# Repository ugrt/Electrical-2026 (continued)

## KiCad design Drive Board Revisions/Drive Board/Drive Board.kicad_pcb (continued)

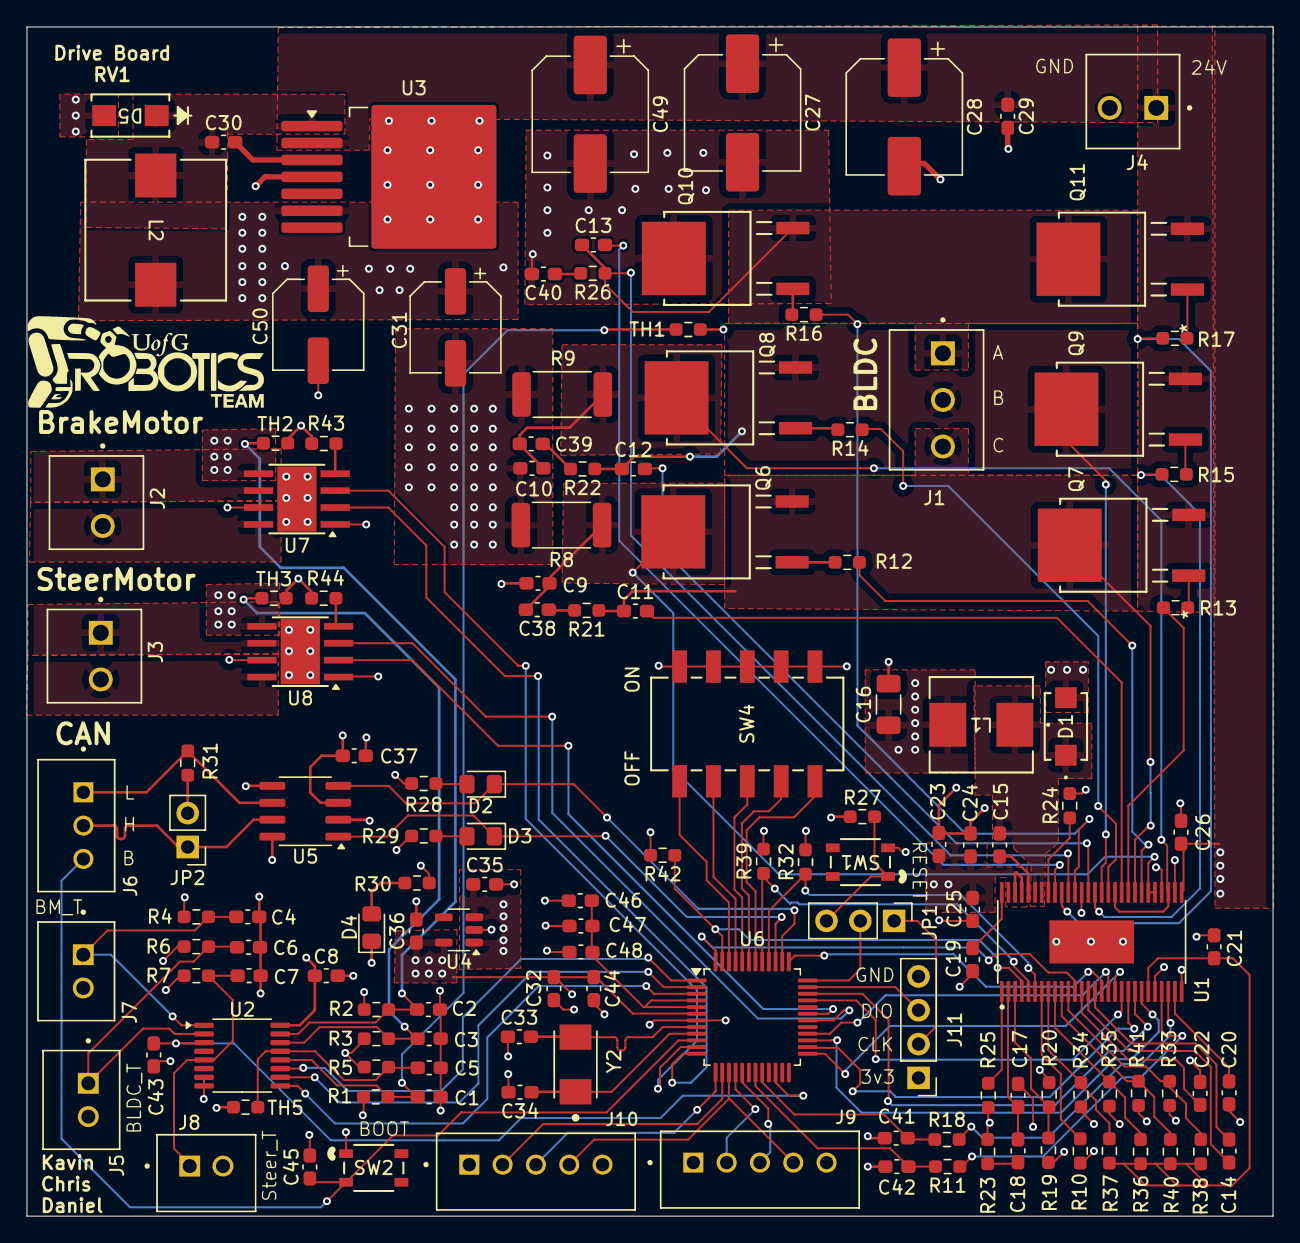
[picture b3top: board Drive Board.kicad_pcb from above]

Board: 4 copper layers, 93.5 x 89.3 mm, 136 parts (0 on the bottom side), 109 nets.

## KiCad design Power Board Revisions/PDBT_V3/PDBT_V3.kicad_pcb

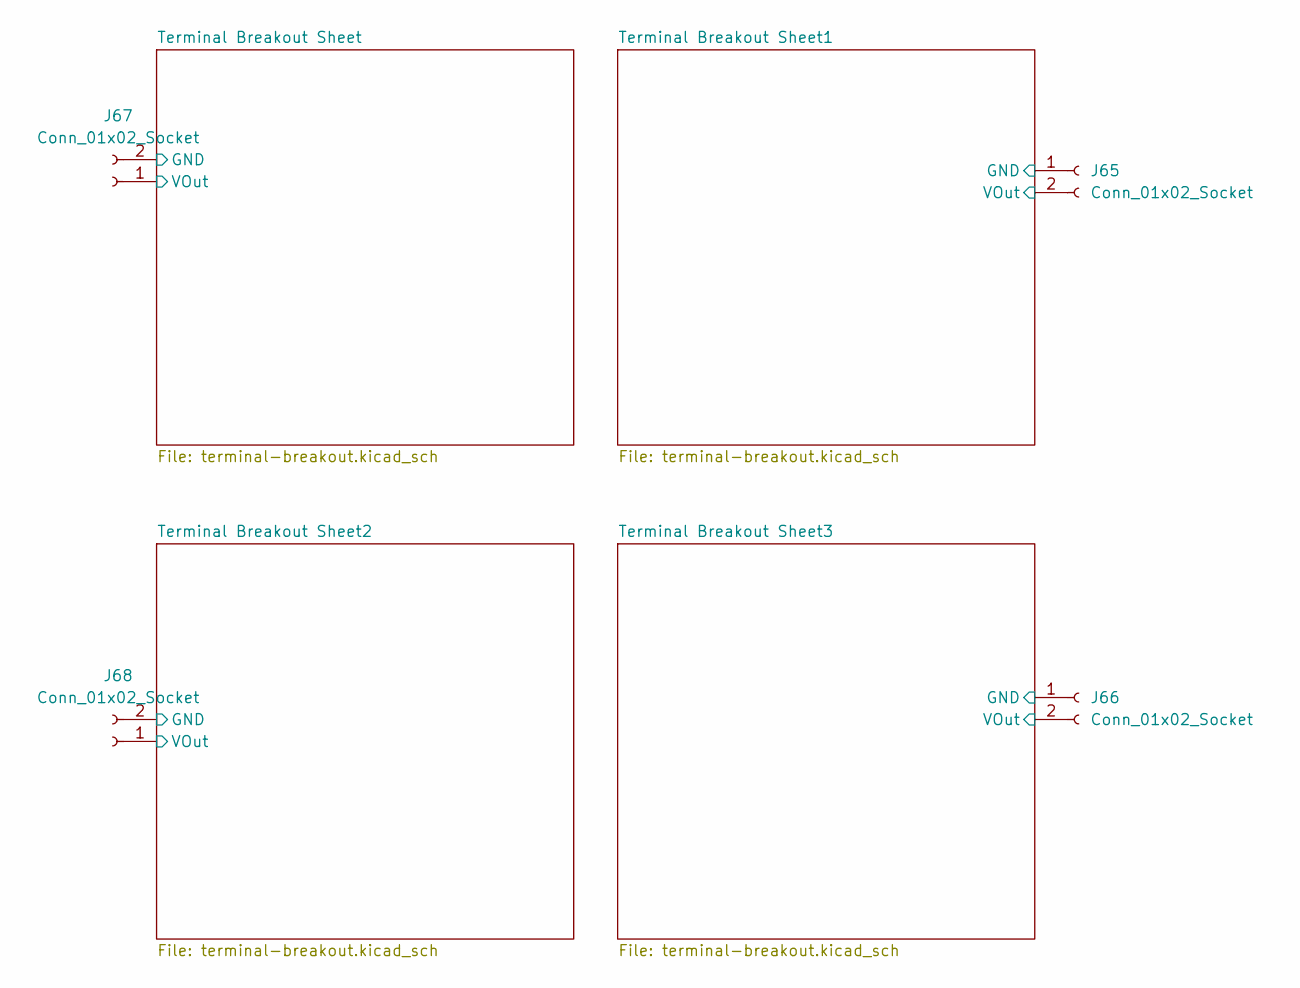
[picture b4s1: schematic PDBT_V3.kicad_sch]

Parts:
J65, J66, J67, J68: Conn_01x02_Socket; AMASS_XT60-F_1x02_P7.20mm_Vertical

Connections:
/Terminal Breakout Sheet1/VOut: J65.2; also elsewhere on the board
/Terminal Breakout Sheet2/VOut: J68.1; also elsewhere on the board
/Terminal Breakout Sheet3/VOut: J66.2; also elsewhere on the board
/Terminal Breakout Sheet/VOut: J67.1; also elsewhere on the board
GND: J65.1, J66.1, J67.2, J68.2; also elsewhere on the board

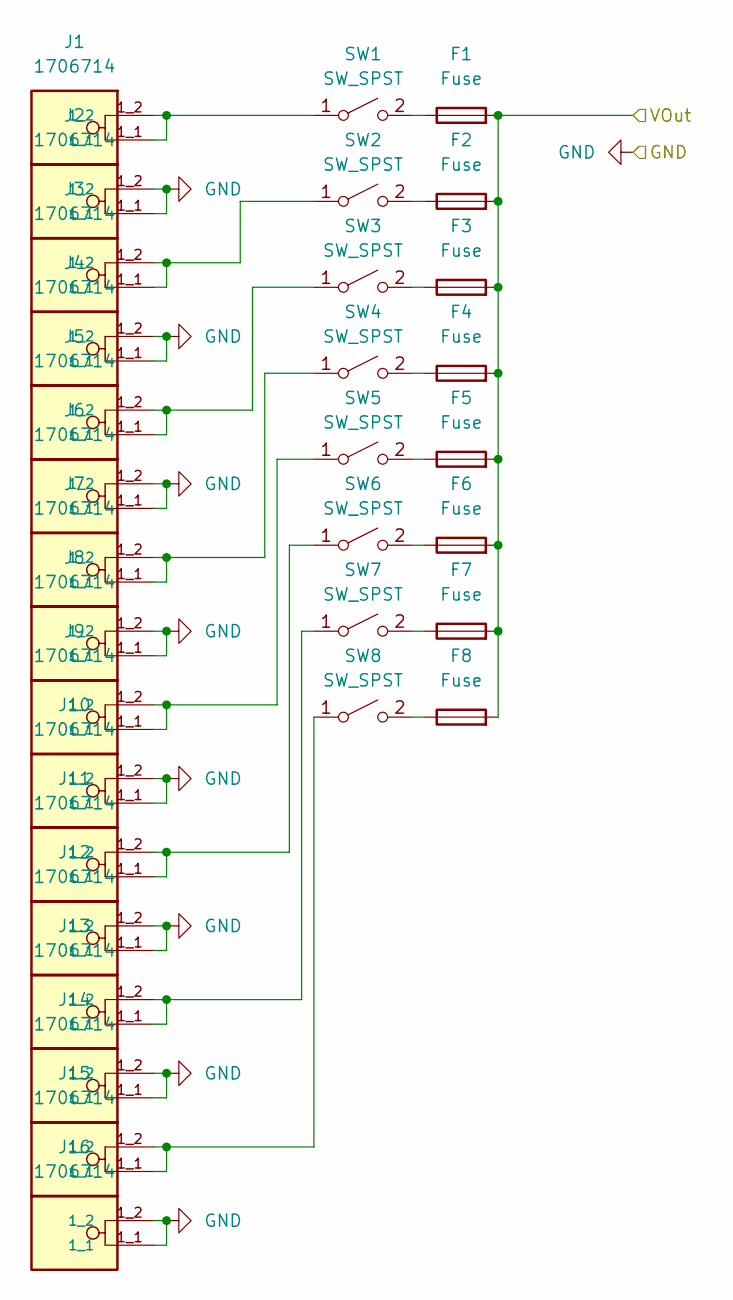
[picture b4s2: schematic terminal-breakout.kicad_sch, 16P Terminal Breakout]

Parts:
F1, F2, F3, F4, F5, F6, F7, F8: Fuse; FUSE_3557-2; DigiKey_Part_Number 36-3557-2-ND
J1, J2, J3, J4, J5, J6, J7, J8, J9, J10, J11, J12, J13, J14, J15, J16: 1706714; Phoenix 1706714; PARTREV 08.12.2022
SW1, SW2, SW3, SW4, SW5, SW6, SW7, SW8: SW_SPST; ESwitch 1101A4CQEA

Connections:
/Terminal Breakout Sheet/VOut: F1.2, F2.2, F3.2, F4.2, F5.2, F6.2, F7.2, F8.2; also elsewhere on the board
GND: J2.1_1, J2.1_2, J4.1_1, J4.1_2, J6.1_1, J6.1_2, J8.1_1, J8.1_2, J10.1_1, J10.1_2, J12.1_1, J12.1_2, J14.1_1, J14.1_2, J16.1_1, J16.1_2; also elsewhere on the board
unnamed: J1.1_1, J1.1_2, SW1.1 (A)
unnamed: F1.1, SW1.2 (B)
unnamed: J3.1_1, J3.1_2, SW2.1 (A)
unnamed: F2.1, SW2.2 (B)
unnamed: J5.1_1, J5.1_2, SW3.1 (A)
unnamed: F3.1, SW3.2 (B)
unnamed: J7.1_1, J7.1_2, SW4.1 (A)
unnamed: F4.1, SW4.2 (B)
unnamed: J9.1_1, J9.1_2, SW5.1 (A)
unnamed: F5.1, SW5.2 (B)
unnamed: J11.1_1, J11.1_2, SW6.1 (A)
unnamed: F6.1, SW6.2 (B)
unnamed: J13.1_1, J13.1_2, SW7.1 (A)
unnamed: F7.1, SW7.2 (B)
unnamed: J15.1_1, J15.1_2, SW8.1 (A)
unnamed: F8.1, SW8.2 (B)

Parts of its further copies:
F9, F10, F11, F12, F13, F14, F15, F16, F17, F18, F19, F20, F21, F22, F23, F24, F25, F26, F27, F28, F29, F30, F31, F32: Fuse; FUSE_3557-2; DigiKey_Part_Number 36-3557-2-ND
J17, J18, J19, J20, J21, J22, J23, J24, J25, J26, J27, J28, J29, J30, J31, J32, J33, J34, J35, J36, J37, J38, J39, J40, J41, J42, J43, J44, J45, J46, J47, J48, J49, J50, J51, J52, J53, J54, J55, J56, J57, J58, J59, J60, J61, J62, J63, J64: 1706714; Phoenix 1706714; PARTREV 08.12.2022
SW9, SW10, SW11, SW12, SW13, SW14, SW15, SW16, SW17, SW18, SW19, SW20, SW21, SW22, SW23, SW24, SW25, SW26, SW27, SW28, SW29, SW30, SW31, SW32: SW_SPST; ESwitch 1101A4CQEA

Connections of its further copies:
/Terminal Breakout Sheet1/VOut: F9.2, F10.2, F11.2, F12.2, F13.2, F14.2, F15.2, F16.2; also elsewhere on the board
/Terminal Breakout Sheet2/VOut: F17.2, F18.2, F19.2, F20.2, F21.2, F22.2, F23.2, F24.2; also elsewhere on the board
/Terminal Breakout Sheet3/VOut: F25.2, F26.2, F27.2, F28.2, F29.2, F30.2, F31.2, F32.2; also elsewhere on the board
GND: J18.1_1, J18.1_2, J20.1_1, J20.1_2, J22.1_1, J22.1_2, J24.1_1, J24.1_2, J26.1_1, J26.1_2, J28.1_1, J28.1_2, J30.1_1, J30.1_2, J32.1_1, J32.1_2, J34.1_1, J34.1_2, J36.1_1, J36.1_2, J38.1_1, J38.1_2, J40.1_1, J40.1_2, J42.1_1, J42.1_2, J44.1_1, J44.1_2, J46.1_1, J46.1_2, J48.1_1, J48.1_2, J50.1_1, J50.1_2, J52.1_1, J52.1_2, J54.1_1, J54.1_2, J56.1_1, J56.1_2, J58.1_1, J58.1_2, J60.1_1, J60.1_2, J62.1_1, J62.1_2, J64.1_1, J64.1_2; also elsewhere on the board
unnamed: J17.1_1, J17.1_2, SW9.1 (A)
unnamed: F9.1, SW9.2 (B)
unnamed: J19.1_1, J19.1_2, SW10.1 (A)
unnamed: F10.1, SW10.2 (B)
unnamed: J21.1_1, J21.1_2, SW11.1 (A)
unnamed: F11.1, SW11.2 (B)
unnamed: J23.1_1, J23.1_2, SW12.1 (A)
unnamed: F12.1, SW12.2 (B)
unnamed: J25.1_1, J25.1_2, SW13.1 (A)
unnamed: F13.1, SW13.2 (B)
unnamed: J27.1_1, J27.1_2, SW14.1 (A)
unnamed: F14.1, SW14.2 (B)
unnamed: J29.1_1, J29.1_2, SW15.1 (A)
unnamed: F15.1, SW15.2 (B)
unnamed: J31.1_1, J31.1_2, SW16.1 (A)
unnamed: F16.1, SW16.2 (B)
unnamed: J33.1_1, J33.1_2, SW17.1 (A)
unnamed: F17.1, SW17.2 (B)
unnamed: J35.1_1, J35.1_2, SW18.1 (A)
unnamed: F18.1, SW18.2 (B)
unnamed: J37.1_1, J37.1_2, SW19.1 (A)
unnamed: F19.1, SW19.2 (B)
unnamed: J39.1_1, J39.1_2, SW20.1 (A)
unnamed: F20.1, SW20.2 (B)
unnamed: J41.1_1, J41.1_2, SW21.1 (A)
unnamed: F21.1, SW21.2 (B)
unnamed: J43.1_1, J43.1_2, SW22.1 (A)
unnamed: F22.1, SW22.2 (B)
unnamed: J45.1_1, J45.1_2, SW23.1 (A)
unnamed: F23.1, SW23.2 (B)
unnamed: J47.1_1, J47.1_2, SW24.1 (A)
unnamed: F24.1, SW24.2 (B)
unnamed: J49.1_1, J49.1_2, SW25.1 (A)
unnamed: F25.1, SW25.2 (B)
unnamed: J51.1_1, J51.1_2, SW26.1 (A)
unnamed: F26.1, SW26.2 (B)
unnamed: J53.1_1, J53.1_2, SW27.1 (A)
unnamed: F27.1, SW27.2 (B)
unnamed: J55.1_1, J55.1_2, SW28.1 (A)
unnamed: F28.1, SW28.2 (B)
unnamed: J57.1_1, J57.1_2, SW29.1 (A)
unnamed: F29.1, SW29.2 (B)
unnamed: J59.1_1, J59.1_2, SW30.1 (A)
unnamed: F30.1, SW30.2 (B)
unnamed: J61.1_1, J61.1_2, SW31.1 (A)
unnamed: F31.1, SW31.2 (B)
unnamed: J63.1_1, J63.1_2, SW32.1 (A)
unnamed: F32.1, SW32.2 (B)

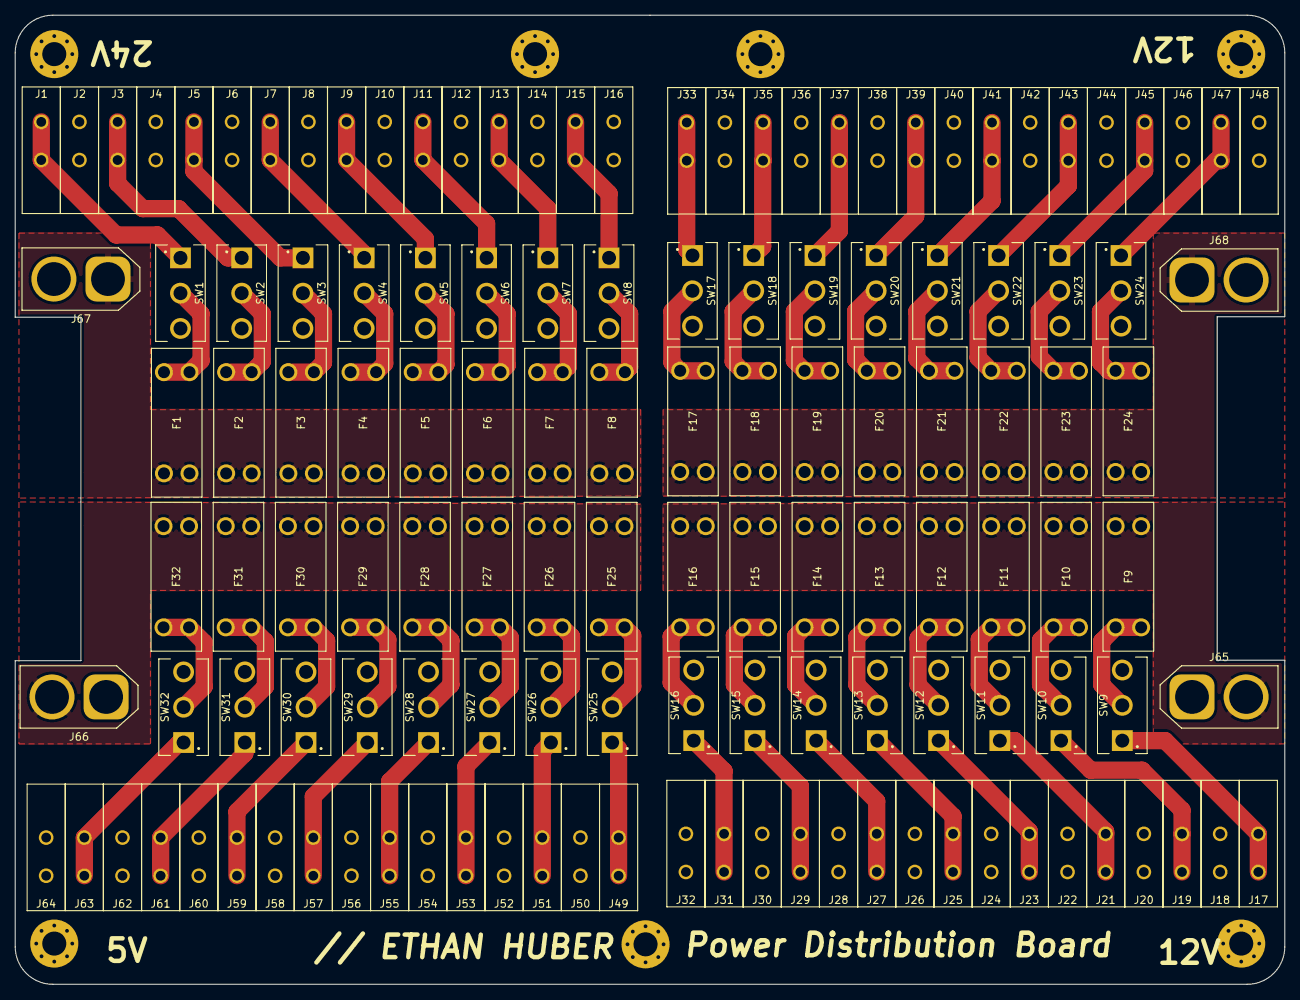
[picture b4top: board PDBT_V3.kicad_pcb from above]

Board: 2 copper layers, 169.0 x 129.0 mm, 139 parts (0 on the bottom side), 69 nets.

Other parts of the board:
H1, H1#2, H1#3, H1#4, H3, H3#2, H4: MountingHole; MountingHole_3.2mm_M3_Pad_Via

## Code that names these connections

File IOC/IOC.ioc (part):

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Mcu.Name=STM32G0B1C(B-C-E)Tx
Mcu.Package=LQFP48
Mcu.UserName=STM32G0B1CETx
PA0.GPIOParameters=GPIO_Label
PA0.GPIO_Label=Brake_IN1
PA0.Signal=S_TIM2_CH1_ETR
PA1.GPIOParameters=GPIO_Label
PA1.GPIO_Label=Brake_IN2
PA1.Signal=S_TIM2_CH2
PA10.Signal=S_TIM1_CH3
PA13.Mode=Serial_Wire
PA13.Signal=SYS_SWDIO
PA14-BOOT0.Mode=Serial_Wire
PA14-BOOT0.Signal=SYS_SWCLK
PA15.GPIOParameters=GPIO_Label
PA15.GPIO_Label=BLDC EN_GATE
PA15.Signal=GPIO_Output
PA2.GPIOParameters=GPIO_Label
PA2.GPIO_Label=EncoderB_DO
PA2.Signal=GPIO_Output
PA3.GPIOParameters=GPIO_Label
PA3.GPIO_Label=EncoderB_Prog
PA3.Signal=GPIO_Input
PA4.GPIOParameters=GPIO_Label
PA4.GPIO_Label=Encoder_CLK
PA4.Signal=GPIO_Output
PA5.GPIOParameters=GPIO_Label
PA5.GPIO_Label=EncoderA_DO
PA5.Signal=GPIO_Input
PA6.GPIOParameters=GPIO_Label
PA6.GPIO_Label=EncoderA_Prog
PA6.Signal=GPIO_Output
PA8.Signal=S_TIM1_CH1
PA9.Signal=S_TIM1_CH2
PB0.GPIOParameters=GPIO_Label
PB0.GPIO_Label=BLDC SO1
PB0.Signal=GPIO_Input
PB1.GPIOParameters=GPIO_Label
PB1.GPIO_Label=BLDC SO2
PB1.Signal=GPIO_Input
PB10.GPIOParameters=GPIO_Label
PB10.GPIO_Label=Temp Output
PB10.Mode=IN11
PB10.Signal=ADC1_IN11
PB13.Mode=PWM Generation1 CH1 CH1N
PB13.Signal=TIM1_CH1N
PB14.Mode=Output Compare2 CH2 CH2N
PB14.Signal=TIM1_CH2N
PB15.Mode=PWM Generation3 CH3 CH3N
PB15.Signal=TIM1_CH3N
PB3.GPIOParameters=GPIO_Label
PB3.GPIO_Label=DIP0
PB3.Signal=GPIO_Input
PB4.GPIOParameters=GPIO_Label
PB4.GPIO_Label=DIP1
PB4.Signal=GPIO_Input
PB5.GPIOParameters=GPIO_Label
PB5.GPIO_Label=DIP2
PB5.Signal=GPIO_Input
PB6.GPIOParameters=GPIO_Label
PB6.GPIO_Label=DIP3
PB6.Signal=GPIO_Input
PB7.GPIOParameters=GPIO_Label
PB7.GPIO_Label=DIP4
PB7.Signal=GPIO_Input
PB8.GPIOParameters=GPIO_Label
PB8.GPIO_Label=PWRGD
PB8.Signal=GPIO_Output
PB9.GPIOParameters=GPIO_Label
PB9.GPIO_Label=DC_CAL
PB9.Signal=GPIO_Input
PC13.GPIOParameters=GPIO_Label
PC13.GPIO_Label=MUXA
PC13.Signal=GPIO_Output
PC14-OSC32_IN\ (PC14).GPIOParameters=GPIO_Label
PC14-OSC32_IN\ (PC14).GPIO_Label=MUXB
PC14-OSC32_IN\ (PC14).Signal=GPIO_Output
PC15-OSC32_OUT\ (PC15).GPIOParameters=GPIO_Label
PC15-OSC32_OUT\ (PC15).GPIO_Label=MUXC
PC15-OSC32_OUT\ (PC15).Signal=GPIO_Output
PC6.GPIOParameters=GPIO_Label
PC6.GPIO_Label=Steer_IN2
PC6.Signal=S_TIM3_CH1
PC7.GPIOParameters=GPIO_Label
PC7.GPIO_Label=Steer_IN1
PC7.Signal=S_TIM3_CH2
PD0.Mode=FDCAN_Activate
PD0.Signal=FDCAN1_RX
PD1.Mode=FDCAN_Activate
PD1.Signal=FDCAN1_TX
PD2.GPIOParameters=GPIO_Label
PD2.GPIO_Label=BLDC NFault
PD2.Signal=GPIO_Input
PD3.GPIOParameters=GPIO_Label
PD3.GPIO_Label=BLDC OCTW
PD3.Signal=GPIO_Input
PF0-OSC_IN\ (PF0).Mode=HSE-External-Oscillator
PF0-OSC_IN\ (PF0).Signal=RCC_OSC_IN
PF1-OSC_OUT\ (PF1).Mode=HSE-External-Oscillator
PF1-OSC_OUT\ (PF1).Signal=RCC_OSC_OUT
RCC.HSE_VALUE=8000000
RCC.SYSCLKFreq_VALUE=16000000
board=custom

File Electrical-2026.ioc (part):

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Mcu.Name=STM32G0B1C(B-C-E)Tx
Mcu.Package=LQFP48
Mcu.UserName=STM32G0B1CBTx
PA0.GPIOParameters=GPIO_Label
PA0.GPIO_Label=SenseR-
PA0.Mode=INM
PA0.Signal=COMP1_INM
PA1.GPIOParameters=GPIO_Label
PA1.GPIO_Label=SenseR+
PA1.Mode=INP
PA1.Signal=COMP1_INP
PA10.GPIOParameters=GPIO_Label
PA10.GPIO_Label=BLDC_C_P
PA10.Signal=S_TIM1_CH3
PA11\ [PA9].GPIOParameters=GPIO_Label
PA11\ [PA9].GPIO_Label=DC_CAL
PA11\ [PA9].Signal=GPIO_Output
PA12\ [PA10].GPIOParameters=GPIO_Label
PA12\ [PA10].GPIO_Label=BLDC_OCTW
PA12\ [PA10].Signal=GPIO_Input
PA13.Mode=Serial_Wire
PA13.Signal=SYS_SWDIO
PA14-BOOT0.Mode=Serial_Wire
PA14-BOOT0.Signal=SYS_SWCLK
PA15.GPIOParameters=GPIO_Label
PA15.GPIO_Label=BLDC_EN
PA15.Signal=GPIO_Output
PA2.GPIOParameters=GPIO_Label
PA2.GPIO_Label=EncoderB_PWM
PA2.Signal=GPIO_Input
PA3.GPIOParameters=GPIO_Label
PA3.GPIO_Label=EncoderB_DO
PA3.Signal=GPIO_Output
PA4.GPIOParameters=GPIO_Label
PA4.GPIO_Label=Encoder_CLK
PA4.Signal=GPIO_Output
PA5.GPIOParameters=GPIO_Label
PA5.GPIO_Label=EncoderA_PROG
PA5.Signal=GPIO_Output
PA6.GPIOParameters=GPIO_Label
PA6.GPIO_Label=EncoderA_DO
PA6.Signal=GPIO_Input
PA7.GPIOParameters=GPIO_Label
PA7.GPIO_Label=Motor_IS
PA7.Mode=IN7
PA7.Signal=ADC1_IN7
PA8.GPIOParameters=GPIO_Label
PA8.GPIO_Label=BLDC_A_P
PA8.Signal=S_TIM1_CH1
PA9.GPIOParameters=GPIO_Label
PA9.GPIO_Label=BLDC_B_P
PA9.Signal=S_TIM1_CH2
PB0.GPIOParameters=GPIO_Label
PB0.GPIO_Label=VBAT
PB0.Mode=IN8
PB0.Signal=ADC1_IN8
PB1.GPIOParameters=GPIO_Label
PB1.GPIO_Label=BLDC S0
PB1.Mode=IN9
PB1.Signal=ADC1_IN9
PB10.GPIOParameters=GPIO_Label
PB10.GPIO_Label=Temperature
PB10.Mode=IN11
PB10.Signal=ADC1_IN11
PB13.GPIOParameters=GPIO_Label
PB13.GPIO_Label=BLDC_A_N
PB13.Mode=PWM Generation1 CH1 CH1N
PB13.Signal=TIM1_CH1N
PB14.GPIOParameters=GPIO_Label
PB14.GPIO_Label=BLDC_B_N
PB14.Mode=PWM Generation2 CH2 CH2N
PB14.Signal=TIM1_CH2N
PB15.GPIOParameters=GPIO_Label
PB15.GPIO_Label=BLDC_C_N
PB15.Mode=Output Compare3 CH3 CH3N
PB15.Signal=TIM1_CH3N
PB2.GPIOParameters=GPIO_Label
PB2.GPIO_Label=BLDC S1
PB2.Mode=IN10
PB2.Signal=ADC1_IN10
PB3.GPIOParameters=GPIO_PuPd,GPIO_Label
PB3.GPIO_Label=DIP1
PB3.GPIO_PuPd=GPIO_PULLUP
PB3.Signal=GPIO_Input
PB4.GPIOParameters=GPIO_PuPd,GPIO_Label
PB4.GPIO_Label=DIP2
PB4.GPIO_PuPd=GPIO_PULLUP
PB4.Signal=GPIO_Input
PB5.GPIOParameters=GPIO_PuPd,GPIO_Label
PB5.GPIO_Label=DIP3
PB5.GPIO_PuPd=GPIO_PULLUP
PB5.Signal=GPIO_Input
PB6.GPIOParameters=GPIO_PuPd,GPIO_Label
PB6.GPIO_Label=DIP4
PB6.GPIO_PuPd=GPIO_PULLUP
PB6.Signal=GPIO_Input
PB7.GPIOParameters=GPIO_Label
PB7.GPIO_Label=Steer_Motor_N
PB7.Mode=Output Compare1 CH1 CH1N
PB7.Signal=TIM17_CH1N
PB8.GPIOParameters=GPIO_Label
PB8.GPIO_Label=PWRGND
PB8.Signal=GPIO_Input
PB9.GPIOParameters=GPIO_Label
PB9.GPIO_Label=Steer_Motor_P
PB9.Signal=S_TIM17_CH1
PC13.GPIOParameters=GPIO_Label
PC13.GPIO_Label=MUXA
PC13.Signal=GPIO_Output
PC14-OSC32_IN\ (PC14).GPIOParameters=GPIO_Label
PC14-OSC32_IN\ (PC14).GPIO_Label=MUXB
PC14-OSC32_IN\ (PC14).Signal=GPIO_Output
PC15-OSC32_OUT\ (PC15).GPIOParameters=GPIO_Label
PC15-OSC32_OUT\ (PC15).GPIO_Label=MUXC
PC15-OSC32_OUT\ (PC15).Signal=GPIO_Output
PC6.GPIOParameters=GPIO_Label
PC6.GPIO_Label=TIM2_CH3_Brake
PC6.Signal=S_TIM2_CH3
PC7.GPIOParameters=GPIO_Label
PC7.GPIO_Label=TIM2_CH4_Brake
PC7.Signal=S_TIM2_CH4
PD0.Mode=FDCAN_Activate
PD0.Signal=FDCAN1_RX
PD1.Mode=FDCAN_Activate
PD1.Signal=FDCAN1_TX
PD2.GPIOParameters=GPIO_Label
PD2.GPIO_Label=BLDC_NFault
PD2.Signal=GPIO_Output
PD3.GPIOParameters=GPIO_PuPd,GPIO_Label
PD3.GPIO_Label=DIP0
PD3.GPIO_PuPd=GPIO_PULLUP
PD3.Signal=GPIO_Input
PF0-OSC_IN\ (PF0).Mode=HSE-External-Oscillator
PF0-OSC_IN\ (PF0).Signal=RCC_OSC_IN
PF1-OSC_OUT\ (PF1).Mode=HSE-External-Oscillator
PF1-OSC_OUT\ (PF1).Signal=RCC_OSC_OUT
RCC.HSE_VALUE=8000000
RCC.SYSCLKFreq_VALUE=16000000
board=custom

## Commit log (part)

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2025-10-09 base project for drive board
2025-11-06 Added Power Distribution Board
2025-11-06 Rev A of PCB
2025-11-06 IOC stuff
2025-11-14 finished RV1 of board
2025-11-20 Add files via upload
    Commit for STM32G0 Prototype board
2025-11-20 Add files via upload
    Arm-board initial upload
2026-01-15 Updated power distribution board
    - Corrected main power connector polarity
    - Added main power connector label
    - Changed LED resistor values
2026-01-18 Updated Power Distro Board & Uploaded Fan Board
2026-02-03 Rover Ready Lightboard
2026-02-12 Final Reference Prototype Board
    Please base your design of this for future STM32G0 embedded PCBs
2026-02-19 cleaned up project directory, maintain naming convention
2026-02-19 second rev of hall effect board
2026-02-19 Add power board revisions
2026-03-05 Transceiver Board Rev1
2026-03-05 finalized layout and fixed repo formatting
2026-03-08 Added V3 Encoder File
    Changes:
    - AS5047P
    -SPI Lines
